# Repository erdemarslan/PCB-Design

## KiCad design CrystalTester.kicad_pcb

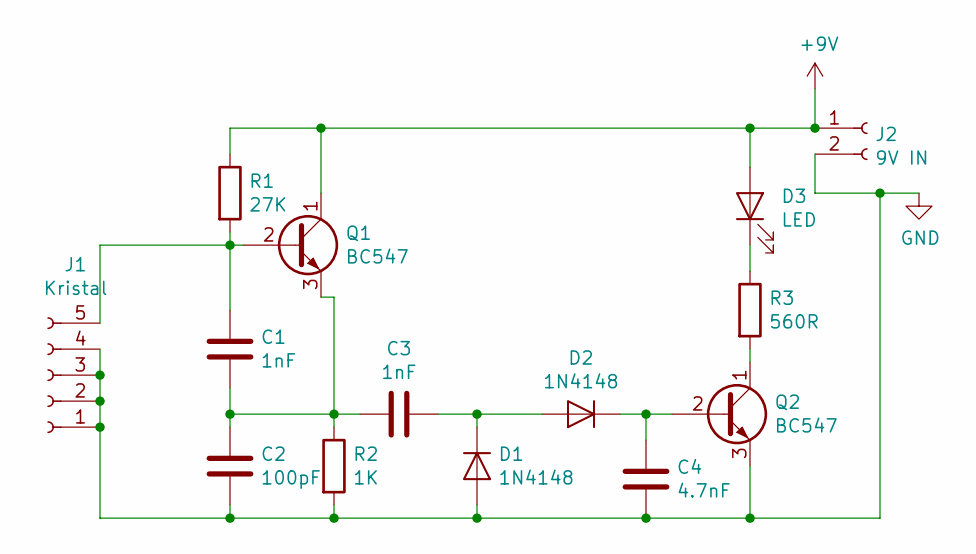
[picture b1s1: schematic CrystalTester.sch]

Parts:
C1, C3: 1nF; C_Disc_D3.0mm_W1.6mm_P2.50mm
C2: 100pF; C_Disc_D3.0mm_W1.6mm_P2.50mm
C4: 4.7nF; C_Disc_D3.0mm_W1.6mm_P2.50mm
D1, D2: 1N4148; D_DO-35_SOD27_P7.62mm_Horizontal
D3: LED; LED_D5.0mm
J1: Kristal; PinHeader_1x05_P2.54mm_Vertical
J2: 9V IN; PinHeader_1x02_P2.54mm_Vertical
Q1, Q2: BC547; TO-92_Inline
R1: 27K; R_Axial_DIN0207_L6.3mm_D2.5mm_P10.16mm_Horizontal
R2: 1K; R_Axial_DIN0207_L6.3mm_D2.5mm_P10.16mm_Horizontal
R3: 560R; R_Axial_DIN0207_L6.3mm_D2.5mm_P10.16mm_Horizontal

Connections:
+9V: D3.2 (A), J2.1, Q1.1 (C), R1.1
GND: C2.2, C4.2, D1.2 (A), J1.1, J1.2, J1.3, J1.4, J2.2, Q2.3 (E), R2.2
unnamed: C1.1, J1.5, Q1.2 (B), R1.2
unnamed: C1.2, C2.1, C3.2, Q1.3 (E), R2.1
unnamed: C3.1, D1.1 (K), D2.2 (A)
unnamed: C4.1, D2.1 (K), Q2.2 (B)
unnamed: D3.1 (K), R3.1
unnamed: Q2.1 (C), R3.2

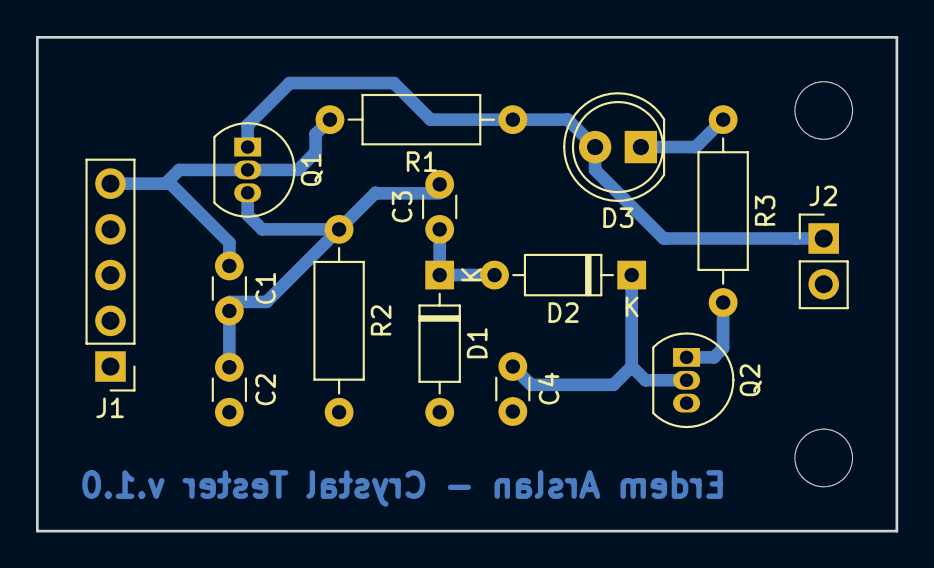
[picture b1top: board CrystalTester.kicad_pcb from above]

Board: 2 copper layers, 47.8 x 27.4 mm, 14 parts (0 on the bottom side), 8 nets.

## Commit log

2019-01-13 Crystal Tester
2019-01-14 UVLed
2019-01-14 UVLed Projector
